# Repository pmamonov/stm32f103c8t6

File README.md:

This software is part of the [ASPAM project](https://github.com/comcon1/ASPAM).

### Установка зависимостей / Install dependencies

```sh
	$ sudo apt-get install make binutils-arm-none-eabi gcc-arm-none-eabi openocd minicom
```

### Клонирование и сборка / Clone & build

```sh
	$ git clone https://github.com/pmamonov/stm32f103c8t6
	$ cd stm32f103c8t6
	$ make -s
```

### Прошивка / Firmware upload

|ST-LINK V2	| STM32 BLUE PILL	|
|---------------|-----------------------|
|GND		| GND			|
|SWCLK		| CLK			|
|SWDIO		| DIO			|

```sh
	$ sudo make load_stlink
```

### Командная строка / CLI access

```sh
	$ sudo minicom -D /dev/ttyACMx # x = 0, 1 ...
	> help
	...
```

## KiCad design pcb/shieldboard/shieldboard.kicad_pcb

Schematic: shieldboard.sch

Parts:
C1: 470,0x16; CP_Radial_D22.0mm_P10.00mm_SnapIn
C2, C3, C4: 0,1; C_0805_2012Metric_Pad1.29x1.40mm_HandSolder
C5: 10,0x16; CP_Radial_D13.0mm_P5.00mm
D1, D2, D3, D4: D; D_SMA_Handsoldering
J1, J2, J3, J4, J5, J6, J7: Conn_01x02; TerminalBlock_bornier-2_P5.08mm
J8, J10: Conn_01x06; PinHeader_1x06_P2.54mm_Vertical
J9: Conn_01x07; PinHeader_1x07_P2.54mm_Vertical
J11: Conn_01x18; PinHeader_1x18_P2.54mm_Vertical
J12: USB_B; USB_B_OST_USB-B1HSxx_Horizontal
J13: Conn_01x01; SolderWirePad_1x01_Drill1mm
M1: LM2596_DC-DC_module
M2: Maple_Mini
Q1, Q2, Q3, Q4: Q_NMOS_GDS; TO-220-3_Vertical
R1, R2, R3, R4: 100; R_0805_2012Metric_Pad1.29x1.40mm_HandSolder
R5: 1,5k; R_0805_2012Metric_Pad1.29x1.40mm_HandSolder
R6, R7: 22; R_0805_2012Metric_Pad1.15x1.40mm_HandSolder
U1: LM7805_TO220; TO-220-3_Vertical

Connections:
+5V: C4.1, C5.1, J7.1, J8.1, J9.5, J10.1, M1.OUT+, M2.18 (5V), U1.3
+12V: C1.1, C2.1, C3.1, D1.1, D2.1, D3.1, D4.1, J1.2, J2.2, J3.2, J4.2, J5.2, J6.2, M1.IN+, U1.1
GND: C1.2, C2.2, C3.2, C4.2, C5.2, J1.1, J2.1, J7.2, J8.6, J9.6, J10.6, J11.1, J11.2, J12.4, M1.IN-, M1.OUT-, M2.19 (G), M2.39 (G), M2.40 (G), Q1.3, Q2.3, Q3.3, Q4.3, U1.2
unnamed: D1.2, J3.1, Q1.2
unnamed: D2.2, J4.1, Q2.2
unnamed: D3.2, J5.1, Q3.2
unnamed: D4.2, J6.1, Q4.2
unnamed: J8.2, M2.B12
unnamed: J8.3, M2.B13
unnamed: J8.4, M2.B14
unnamed: J8.5, M2.B15
unnamed: J9.1, M2.A15
unnamed: J9.2, M2.B3
unnamed: J9.3, M2.B4
unnamed: J9.4, M2.B5
unnamed: J9.7, M2.20 (3.3)
unnamed: J10.2, M2.B6
unnamed: J10.3, M2.B7
unnamed: J10.4, M2.B10
unnamed: J10.5, M2.B11
unnamed: J11.3, M2.38 (3.3)
unnamed: J11.4, M2.R
unnamed: J11.5, M2.B1
unnamed: J11.6, M2.B0
unnamed: J11.7, M2.A7
unnamed: J11.8, M2.A6
unnamed: J11.9, M2.A5
unnamed: J11.10, M2.A4
unnamed: J11.11, M2.A3
unnamed: J11.12, M2.A2
unnamed: J11.13, M2.A1
unnamed: J11.14, M2.A0
unnamed: J11.15, M2.C15
unnamed: J11.16, M2.C14
unnamed: J11.17, M2.C13
unnamed: J11.18, M2.VB
unnamed: J12.1, J13.1
unnamed: J12.2, R7.2
unnamed: J12.3, R6.2
unnamed: M2.A8, R1.1
unnamed: M2.A9, R2.1
unnamed: M2.A10, R5.1
unnamed: M2.A11, R7.1
unnamed: M2.A12, R5.2, R6.1
unnamed: M2.B8, R3.1
unnamed: M2.B9, R4.1
unnamed: Q1.1, R1.2
unnamed: Q2.1, R2.2
unnamed: Q3.1, R3.2
unnamed: Q4.1, R4.2

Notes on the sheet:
BI_1
BI_2
BO_1
BO_2
+12V
-12V
Optional DC-DC module
sensor_port_1
coil_port_1
sensor_port_2
coil_port_2
DESOLDER R10!
R10
PWM_00
PWM_01
PWM_10
PWM_11
SENS_13
SENS_12
SENS_11
SENS_10
SENS_00
SENS_01
SENS_02
SENS_03
GND
+5V

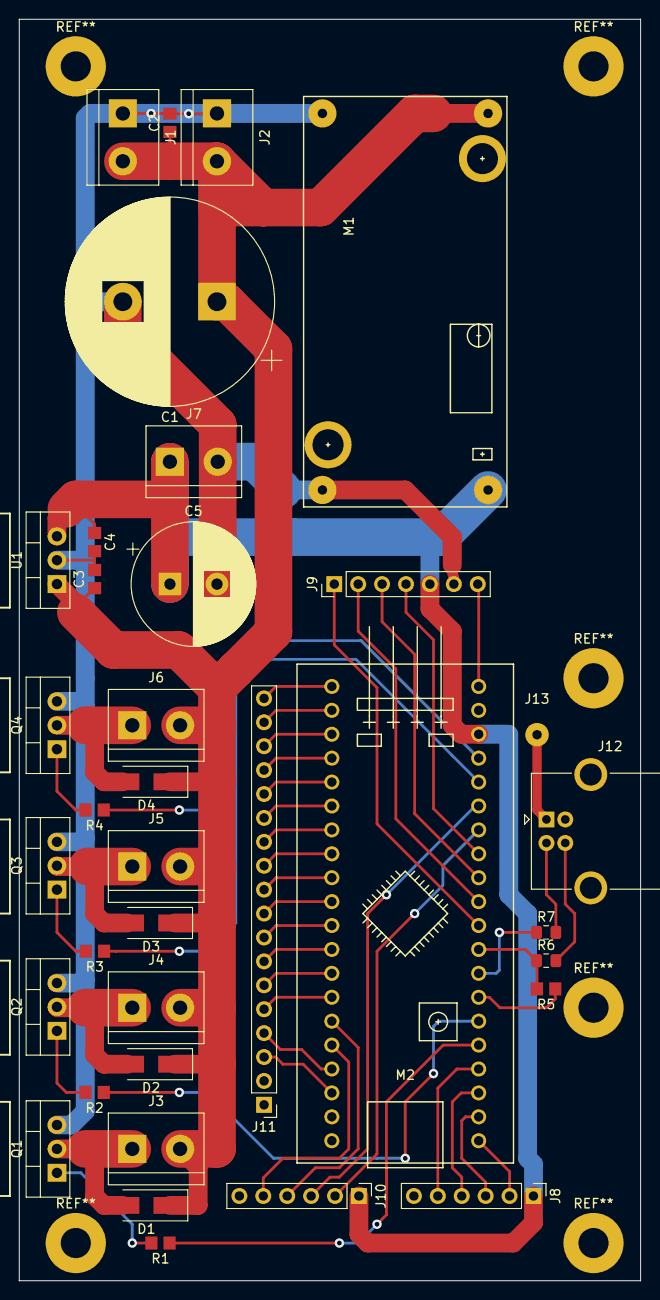
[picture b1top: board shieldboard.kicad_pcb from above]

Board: 2 copper layers, 66.0 x 134.0 mm, 36 parts (0 on the bottom side), 50 nets.

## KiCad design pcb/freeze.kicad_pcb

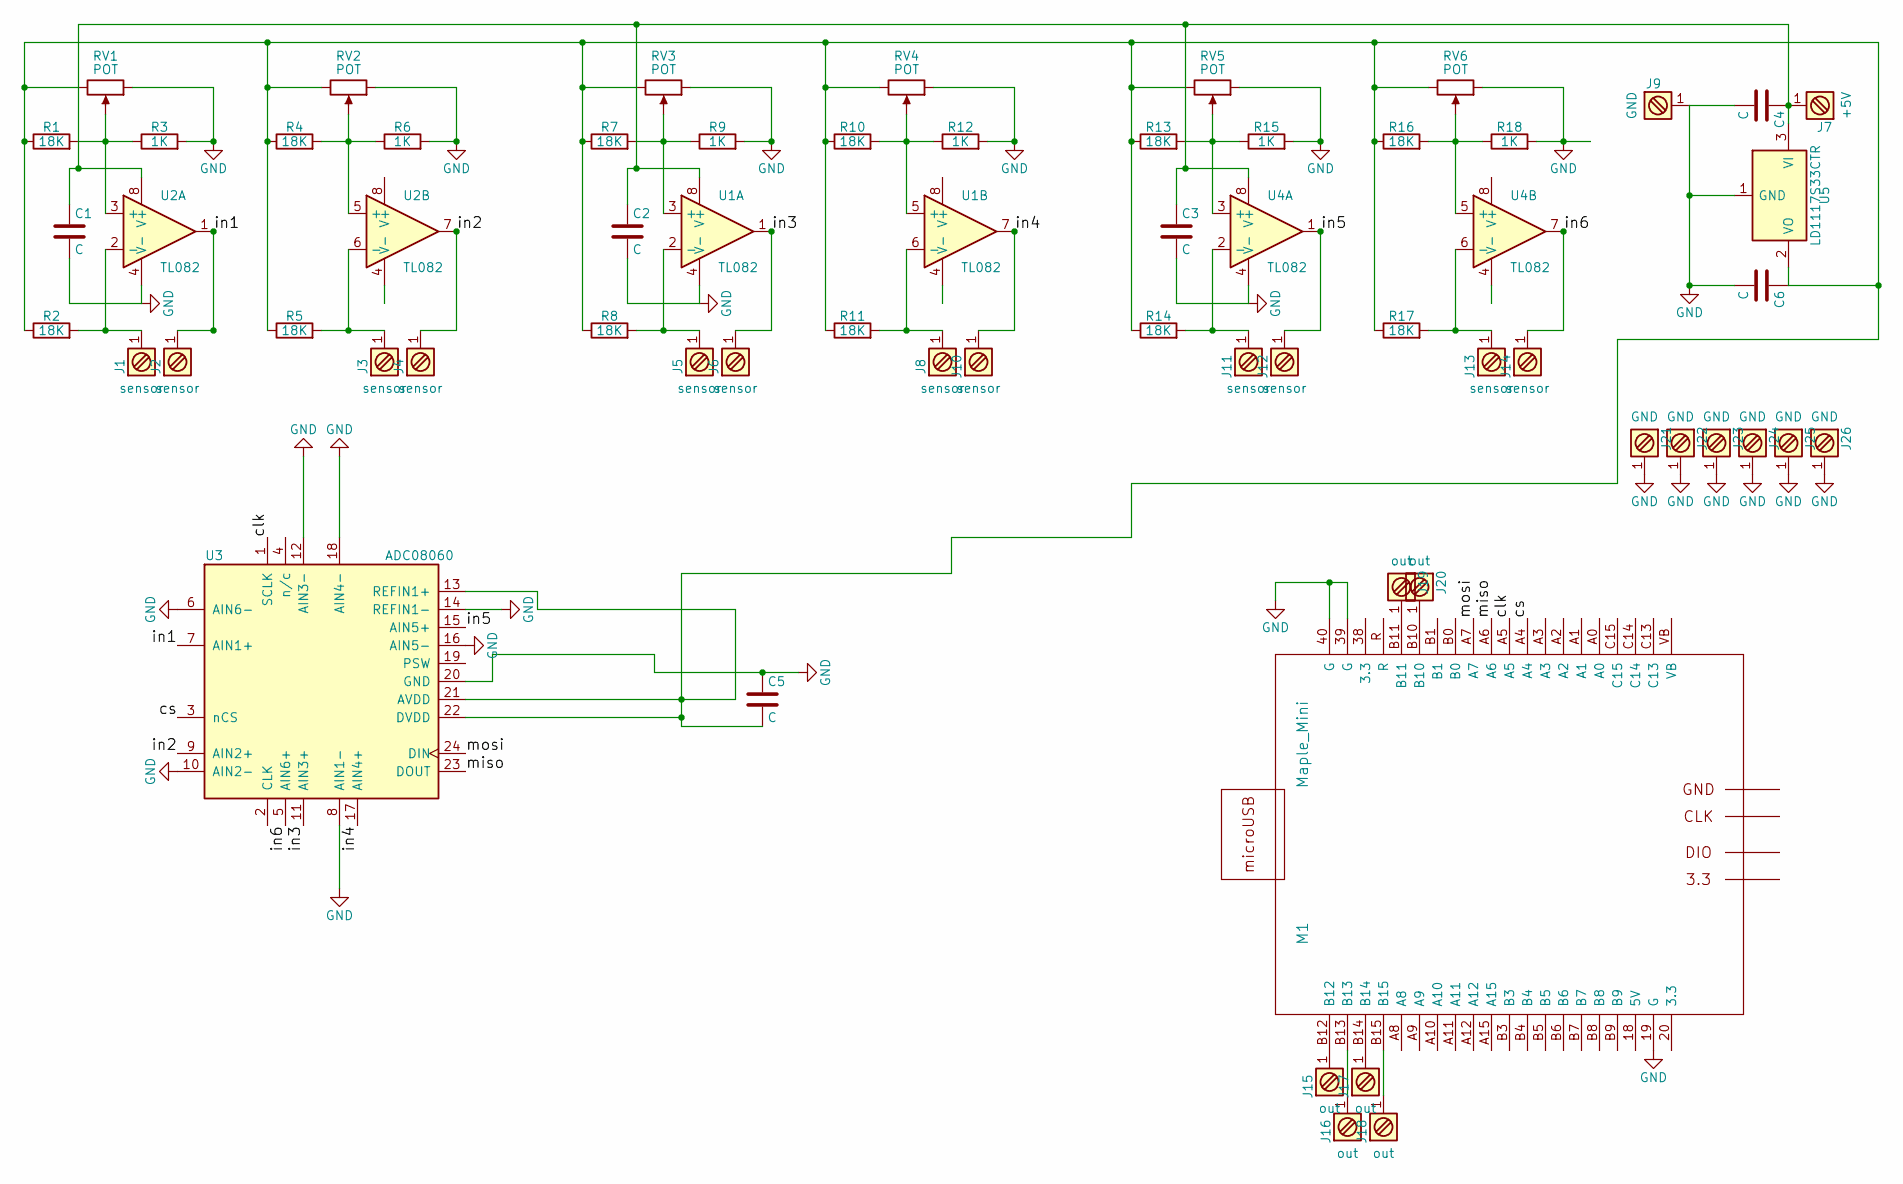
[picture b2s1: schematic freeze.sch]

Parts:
C1, C2, C3, C4, C5, C6: C; C_0805_HandSoldering
J1, J2, J3, J4, J5, J6, J8, J10, J11, J12, J13, J14: sensor; conn_1mm
J7: +5V; conn_1mm
J9, J21, J22, J23, J24, J25, J26: GND; conn_1mm
J15, J16, J17, J18, J19, J20: out; conn_1mm
M1: Maple_Mini
R1, R4, R7, R10, R13, R16: 18K; R_Axial_DIN0207_L6.3mm_D2.5mm_P15.24mm_Horizontal
R2, R5, R8, R11, R14, R17: 18K; R_Axial_DIN0207_L6.3mm_D2.5mm_P10.16mm_Horizontal
R3, R6, R9, R12, R15, R18: 1K; R_Axial_DIN0207_L6.3mm_D2.5mm_P10.16mm_Horizontal
RV1, RV2, RV3, RV4, RV5, RV6: POT; 3296W
U1, U2, U4: TL082; SOIC-8-N
U3: ADC08060; TSSOP-24_4.4x7.8mm_Pitch0.65mm
U5: LD1117S33CTR; SOT-223-3_TabPin2

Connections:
/clk: M1.A5, U3.1 (SCLK)
/cs: M1.A4, U3.3 (nCS)
/in1: J2.1, U2.1, U3.7 (AIN1+)
/in2: J4.1, U2.7, U3.9 (AIN2+)
/in3: J6.1, U1.1, U3.11 (AIN3+)
/in4: J10.1, U1.7, U3.17 (AIN4+)
/in5: J12.1, U3.15 (AIN5+), U4.1
/in6: J14.1, U3.5 (AIN6+), U4.7
/miso: M1.A6, U3.23 (DOUT)
/mosi: M1.A7, U3.24 (DIN)
GND: C1.2, C2.2, C3.2, C4.2, C5.1, C6.2, J9.1, J21.1, J22.1, J23.1, J24.1, J25.1, J26.1, M1.19 (G), M1.39 (G), M1.40 (G), R3.2, R6.2, R9.2, R12.2, R15.2, R18.2, RV1.1, RV2.1, RV3.1, RV4.1, RV5.1, RV6.1, U1.4 (V-), U2.4 (V-), U3.6 (AIN6-), U3.8 (AIN1-), U3.10 (AIN2-), U3.12 (AIN3-), U3.14 (REFIN1-), U3.16 (AIN5-), U3.18 (AIN4-), U3.20 (GND), U4.4 (V-), U5.1 (GND)
unnamed: C1.1, C2.1, C3.1, C4.1, J7.1, U1.8 (V+), U2.8 (V+), U4.8 (V+), U5.3 (VI)
unnamed: C5.2, C6.1, R1.1, R2.1, R4.1, R5.1, R7.1, R8.1, R10.1, R11.1, R13.1, R14.1, R16.1, R17.1, RV1.3, RV2.3, RV3.3, RV4.3, RV5.3, RV6.3, U3.13 (REFIN1+), U3.21 (AVDD), U3.22 (DVDD), U5.2 (VO)
unnamed: J1.1, R2.2, U2.2 (-)
unnamed: J3.1, R5.2, U2.6 (-)
unnamed: J5.1, R8.2, U1.2 (-)
unnamed: J8.1, R11.2, U1.6 (-)
unnamed: J11.1, R14.2, U4.2 (-)
unnamed: J13.1, R17.2, U4.6 (-)
unnamed: J15.1, M1.B12
unnamed: J16.1, M1.B13
unnamed: J17.1, M1.B14
unnamed: J18.1, M1.B15
unnamed: J19.1, M1.B11
unnamed: J20.1, M1.B10
unnamed: R1.2, R3.1, RV1.2, U2.3 (+)
unnamed: R4.2, R6.1, RV2.2, U2.5 (+)
unnamed: R7.2, R9.1, RV3.2, U1.3 (+)
unnamed: R10.2, R12.1, RV4.2, U1.5 (+)
unnamed: R13.2, R15.1, RV5.2, U4.3 (+)
unnamed: R16.2, R18.1, RV6.2, U4.5 (+)

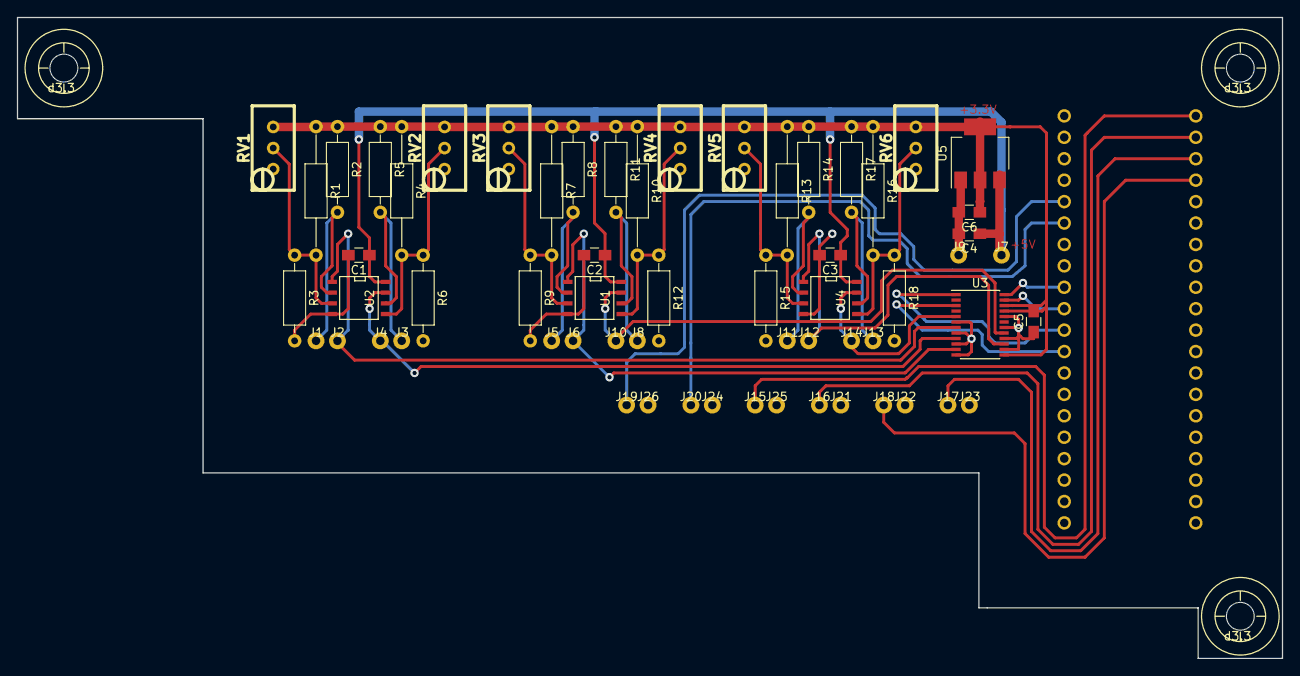
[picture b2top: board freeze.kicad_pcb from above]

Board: 2 copper layers, 150.0 x 76.0 mm, 65 parts (1 on the bottom side), 31 nets.

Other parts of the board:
hole_3.3mm, hole_3.3mm#2, hole_3.3mm#3: d3.3; hole_3.3mm

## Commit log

2017-07-20 add devboard schematic
2017-07-20 stm32f10x_flash: define flash access keys
2017-07-20 adapt for stm32f103c8t6 devboard
2017-07-20 add support for application data storage in system flash
2017-07-20 lcd: fill display with spaces on start
2017-07-20 adc: store calibration in flash
2017-07-20 chat: add `disp` command to control the display
2017-07-20 add I2C LCD display support
    Import code from https://github.com/Vendict/STM32_LCD_I2C
2017-07-20 adc: add support for channels selection in runtime
2017-07-20 chat: add ADC control commands
2017-07-20 adc: implement D6F-P0010A2 flow sensor monitor
    Flow sensor readings are numerically integrated to estimate the volume.
2017-07-20 run at 72MHz
2017-07-20 FreeRTOSConfig: set available RAM size to 16k
2017-07-20 add `cal.sh` script to upload calibration curve to uC
2017-07-20 adc: increase display rate
2017-07-21 cdcio: refactoring
2017-07-21 chat: rename `adc_cal*` commands to `cal*`
2017-07-22 cal.sh: update calibration curve
2017-08-24 add connections info
2017-08-26 fixup! adc: implement D6F-P0010A2 flow sensor monitor
2017-09-07 add CO2 sensor datasheet
2017-09-07 adc: update calibration curve
2017-09-07 lcd: fill display buffer before lcd init
    Fix `disp` command when LCD init hangs (no LCD).
2017-09-07 add flow sensor datasheet
2017-09-07 chat.c: remove dead code
2017-09-08 add CO2 monitor
2017-09-08 fixup! add CO2 monitor
2017-09-08 co2: add sensor responce data and visualization
2017-09-13 adapt for stm32f103c8t6 devboard
    FreeRTOSConfig: set available RAM size to 16k
    run at 72MHz
    cdcio: refactoring
2017-09-13 chat: add `date` command
2017-09-13 chat: add `help` command
2017-09-13 fix flash size
2017-11-01 README.md: add firmware description
2017-11-01 lcd: set screen update period to 200 ticks (ms)
2017-11-01 lcd: print placeholders for missing sensors
2017-11-01 co2: fix display layout
2017-11-01 adc: fix display layout
2017-11-01 adc: add separate calibration and counter for xenon flow
2017-11-01 fixup! README.md: add firmware description
2017-11-02 fixup! adc: add separate calibration and counter for xenon flow
2017-11-05 Revert "lcd: print placeholders for missing sensors"
    This reverts commit 7782c2666b9b0706eaf2b5300d57731e2624d22f.
2017-11-05 add stm32f103* datasheet
2017-11-05 add lm2596 datasheet
2017-11-05 WIP: implement main control algorithm
2017-11-11 add script to dump calibration data
2017-11-11 chat: fix \x0 at the end of the prompt
2017-11-11 fixup! fixup! adc: add separate calibration and counter for xenon flow
2017-11-12 lcd: move lcd init code to lcd_init()
2017-11-12 allocate PB9 as a pull-up for USB DP
2017-11-12 fixup! WIP: implement main control algorithm
2017-11-12 lcd: dump to CDC periodically
2017-11-12 Makefile: add reset target
2017-11-12 fixup! lcd: dump to CDC periodically
2017-11-13 Makefile: add load_stlink target
2017-11-13 Makefile: no need for CXX
2017-11-18 newlib_stubs: fix missing stdint.h include
2017-11-18 fixup! Makefile: add load_stlink target
2017-11-18 fixup! fixup! fixup! adc: add separate calibration and counter for xenon flow
2017-11-18 fixup! fixup! Makefile: add load_stlink target
2017-11-18 i2c_lcd: don't hang, return error on timeout
2017-11-18 lcd: re-initialize display on error
2017-11-18 FreeeRTOS: decrease heap size by 2k to leave more room for data+bss
2017-11-18 lcd: fix update timings
2017-11-19 fixup! i2c_lcd: don't hang, return error on timeout
2017-11-19 fixup! lcd: re-initialize display on error
2017-11-28 lcd: fix race condition in lcd_setstr
2017-12-07 Makefile: add reset[_stlink] target
2017-12-07 fixup! lcd: fix update timings
2017-12-07 remove dead code
2017-12-09 lcd: dump lcd charset
2017-12-10 lcd: snowfall
2017-12-10 lcd: bubbles
2017-12-10 fixup! lcd: snowfall
2017-12-10 Revert "fixup! lcd: snowfall"
    This reverts commit 730fa924a9b7073e3fe4ece3207a535dfc04ca96.
2018-01-05 disable LCD display support
2018-01-05 add support for PWM
2018-01-05 main: init PWM0..2 (TIM1/CH1..3, PA8..10) @ 10kHz
2018-01-05 chat: add pwm command to control PWM's
2018-07-05 blink: export blink_init() and blink_toggle()
2018-07-05 chat: add blink command
2018-07-05 main: disable blink and lcd tasks, call blink_init()
2018-07-05 add blink.py
2018-07-07 add pcb zygote
2018-07-28 main: remove lcd task
2018-07-28 add pcb
2018-07-28 add AD779x library and wrapper
2018-07-28 add ADC datasheet
2018-07-28 APB2 @ 4.5 MHz, SPI1 @ 17.5 kHz
2018-07-28 chat: add ADC commands
2018-07-28 fixup! add AD779x library and wrapper
2018-07-28 chat: add spi command
2018-07-28 fixup! chat: add ADC commands
2018-07-28 ad779x_stm32: spi_rx: empty rx buffer before read
2018-07-28 ad779x_stm32: skip calibration
2018-07-28 fixup! chat: add spi command
2018-07-28 fixup! fixup! chat: add ADC commands
2018-07-28 fixup! fixup! chat: add spi command
2018-07-28 chat: make error message contructive
2018-07-28 fixup! fixup! add AD779x library and wrapper
2018-07-28 fixup! fixup! fixup! add AD779x library and wrapper
2018-07-28 fixup! fixup! fixup! fixup! add AD779x library and wrapper
2018-07-28 add aquarium.py
2018-07-29 ad779x_stm32: disable gain
2018-07-29 ad779x_stm32: add support for channel selection
2018-07-29 update ad779x submodule
2018-07-29 ad779x_stm32: set unipolar mode
2018-07-29 data: measure aperture and noise
2018-07-30 add GPIO wrapper
2018-07-30 chat: add `gpio` command
2018-07-30 chat: fix commands list printing
2018-07-31 fixup! add GPIO wrapper
2018-07-31 fixup! add aquarium.py
2018-07-31 aquarium.py: add `gpio()` method
2018-08-03 fixup! ad779x_stm32: set unipolar mode
2018-08-03 fixup! chat: add `gpio` command
2018-08-03 main: start gpio_reset_task()
2018-08-03 fixup! aquarium.py: add `gpio()` method
2018-08-03 chat: make error message constructive
2018-08-12 ad779x_stm32: init: accept gain value as a second argument
2018-08-12 chat: adc_init: accept gain value as a second arg
2018-08-19 Well. I'm hre and I have commited the thermostat.py script.
2018-08-19 Period of averaging enlarged.
2018-08-20 Some bug were fixed
2018-08-21 chat: initialize cmd_list[] properly
2018-08-22 chat: add command to disable echo
2018-08-25 chat: change default output
2018-08-25 add README.md
2018-09-04 Revert "add pcb zygote"
    This reverts commit c6b03261f67118e9d1d9802cb595fd21bd381b43.
2018-09-04 allocate PA10 as a pull-up for USB DP
2018-09-04 add pcb design files
2018-09-04 chat: add pwm command to control PWMs
2018-09-04 main: init PWMs @ 10kHz
2018-09-04 gpio: bind gpios for the maze
2018-09-04 README: add connections list
2018-09-04 fixup! add support for PWM
2018-09-04 main: init gpio and start gpio polling task
2018-09-04 chat: disable echo
2018-09-05 pwm: bind PWMs for the maze
2018-09-06 chat: pwm: suppress output
2018-10-12 chat: add gpio command
2018-10-12 WIP: add gate control script
2018-10-12 gpio: add pin for transporder charger control
2018-10-12 maze: use `gpio` command to read current gpio state
2018-10-12 maze: add transponder charger control
2018-10-13 fixup! WIP: add gate control script
2018-10-17 fixup! fixup! WIP: add gate control script
2018-10-18 maze.py: fix echo disable procedure
2018-10-18 maze.py: introduce state tags
2018-10-31 maze.py: "refresh" doors' locks periodically
2018-10-31 fixup! maze.py: "refresh" doors' locks periodically
2018-11-02 maze.py: don't take into account d1 sensor for OUT <-> WAIT transitions
2018-11-07 add license info
2018-11-07 WIP: imlement pulse counter
2018-11-07 USB DP pull-up @ A10
2018-11-07 chat: add `adc` command
2018-11-07 README.md: add reference to the parent project repo
2018-11-10 fwload.openocd: fix flash size
2018-11-17 blink: implement soft pwm for smooth blinking
2018-11-17 gpio: implement gpio_pwm_task()
2018-11-17 main: start gpio_pwm_task()
2018-11-17 gpio: attach 8 dot LED panel
2018-11-17 gpio: blink demo
2018-11-17 gpio: bounce demo
2018-11-17 gpio: trace demo
2018-11-20 fixup! gpio: trace demo
2018-11-20 gpio: periodic trace demo
2018-11-27 implement rx test
2018-11-29 implement tx test
2018-12-04 adc: init: reset ADC
2018-12-04 FreeRTOS: set heap size to 8k
2018-12-04 main: increase vChatTask stack size up to 512 words
2018-12-04 adc: save channel mask
2018-12-04 blink: export LED control functions
2018-12-04 adc: implement continuous ADC data acquisition using DMA
    Sample rate ~220kHz.
2018-12-09 adc: set DMA buffer size to 8k
2018-12-09 chat: add `xadc` command + relevant python scripts
2018-12-27 FIXME: maze.py: workaround firmware bug
    TODO: add locking to cdc_write_buf
2018-12-28 maze.py: add support for output gate
2019-04-25 implement I2C helpers
2019-04-25 chat: implement `i2cdetect` command
2019-04-25 chat: add `co2` command to read T67xx CO2 sensor
2019-04-29 fixup! chat: add `co2` command to read T67xx CO2 sensor
2019-04-29 fixup! implement I2C helpers
2019-05-01 chat: add `temp` command to read adt7420
2019-05-01 chat: add `ht` command to read htu21d sensor
2019-06-29 add temp.py
2019-10-26 use stlink
2021-05-05 chat: remove `disp` command
2021-05-05 main: move usb_dp_pu() call to USB_Init()
2021-05-05 cdcio: implement cdc_read(), cdc_write()
2021-05-05 chat: use supplied callbacks for read/write
2021-05-07 add circular buffer manipulation functions
2021-05-07 add UART support
2021-05-07 fixup! add UART support
2021-05-08 chat: refactoring
    - use supplied readline/puts funcs
    - no echo
    - unknown commands are ignored
    For interactive usage run:
    $ picocom -c --omap crcrlf ...
2021-05-08 introduce `common.h`
2021-05-09 gpio: allocate GPIOs for BT
    B0: disconnect
    B1: link status
2021-05-09 run @ 8MHz
2021-05-09 chat: add BT stuff
2021-05-09 WIP: add support for Seeed Studio Bluetooth shiled v1.1
2021-05-09 main: run `chat` via BT @ UART3; use UART2 for debug
2021-05-09 blink: fix freq
2021-05-09 WIP: enable ADC
2021-05-09 adc: implement adc_get_mv() using internal voltage reference
2021-05-09 chat: add command for battery monitoring
2021-05-11 cbuf: call vTaskDelay() if no data availavle
2021-05-11 FreeRTOS: enable tickless idle
2021-05-11 blink: reduce ON time
2021-05-11 fixup! chat: add command for battery monitoring
2021-05-13 battery consumption
